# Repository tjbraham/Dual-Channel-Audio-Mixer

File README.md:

# Dual-Channel 3-Band Analog Audio Mixer PCB

A custom single-supply ($9\text{ V}$) dual-channel analog audio mixer featuring a 3-band Linkwitz-Riley ($Q = 0.5$) Sallen-Key active crossover network, $180^\circ$ mid-band phase inversion for flat summation, and an inverting summing architecture designed in **LTspice** and **KiCad** for automated SMT assembly.

---

## Hardware Overview & Key Specifications

| Parameter | Specification |
| :--- | :--- |
| **Channels** | 2 Independent Stereo-to-Mono Input Channels (`J7`, `J8`) + 1 Master Output (`J9`) |
| **Filter Topology** | 2nd-Order Unity-Gain Sallen-Key Active Crossover ($Q = 0.5$, $-6\text{ dB}$ at $f_c$) |
| **Frequency Bands** | **Low:** $< 102.6\text{ Hz}$ \| **Mid:** $102.6\text{ Hz} - 4.98\text{ kHz}$ \| **High:** $> 4.98\text{ kHz}$ |
| **Active ICs** | $4\times$ `TL074CDT` Quad JFET-Input Operational Amplifiers (`SOIC-14`) |
| **Power Supply** | $9\text{ V}$ Single-Supply (`BT1` / `SW1`) with $4.5\text{ V}$ Virtual Ground (`VRef`) |
| **PCB Dimensions** | $87.11\text{ mm} \times 51.33\text{ mm}$ ($3.43\text{ in} \times 2.02\text{ in}$), 2-Layer `FR-4` ($1.6\text{ mm}$, $1\text{ oz}$ Cu) |
| **Component Count** | 89 Total Designators (69 `0805`/`SOIC-14` SMD Parts + 20 Through-Hole/DFT Items) |

---

## Circuit Architecture & Engineering Decisions

### 1. Input Stage & Single-Supply Virtual Reference (`VRef`)
* **Passive Stereo-to-Mono Input Summing:** Each $3.5\text{ mm}$ TRS input jack (`J7` and `J8`) sums Left (Tip) and Right (Ring) channels through matched $1\text{ k}\Omega$ resistors (`R10`/`R11` and `R20`/`R21`), providing a $500\ \Omega$ effective source impedance before AC coupling through $10\ \mu\text{F}$ capacitors (`C2`, `C3`) and biasing to `VRef` via $1\text{ M}\Omega$ resistors (`R9`, `R22`).
* **Virtual Ground Generation (`VRef = 4.5V`):** Because the circuit operates from a single $9\text{ V}$ battery (`BT1`), a $10\text{ k}\Omega / 10\text{ k}\Omega$ voltage divider (`R3`, `R4`) bypassed with a $10\ \mu\text{F}$ capacitor (`C1`, $f_c = 3.18\text{ Hz}$) establishes a low-noise $4.5\text{ V}$ mid-rail reference (`VRef`) for all op-amp non-inverting inputs and filter bias paths.
* **Click-Free Potentiometer Biasing:** All six $10\text{ k}\Omega$ band-level potentiometers (`RV1`–`RV6`) tie their reference terminals directly to `VRef` rather than `GND`. Keeping the wiper and the op-amp summing nodes at an identical $4.5\text{ V}$ DC potential eliminates DC current flow through the potentiometer wipers, preventing scratchy audio noise when adjusting EQ levels.

### 2. 3-Band Sallen-Key Crossover & Impedance Scaling
Each input channel splits into three parallel active filter branches designed around equal-$`R`$, equal-$`C`$ unity-gain Sallen-Key topologies ($Q = 0.5$):
* **Low-Pass Band (`U1A`, `U2C`):** Uses $R = 3.3\text{ k}\Omega$ (`R26`/`R27`, `R12`/`R13`) and $C = 470\text{ nF}$ (`C9`/`C10`, `C21`/`C22`) to set a cutoff frequency of:
  $$f_{c,\text{LP}} = \frac{1}{2\pi (3.3\text{ k}\Omega)(470\text{ nF})} = 102.61\text{ Hz}$$
* **High-Pass Band (`U1B`, `U2D`) & Impedance Scaling:** Uses $C = 4.7\text{ nF}$ (`C13`/`C14`, `C5`/`C7`) and $R = 6.8\text{ k}\Omega$ (`R30`/`R31`, `R14`/`R42`) to set a cutoff frequency of:
  $$f_{c,\text{HP}} = \frac{1}{2\pi (6.8\text{ k}\Omega)(4.7\text{ nF})} = 4979.82\text{ Hz}$$
  Scaling the high-frequency filter impedances up by $100\times$ (from $68\ \Omega / 470\text{ nF}$ to $6.8\text{ k}\Omega / 4.7\text{ nF}$) prevents the high-pass stage from loading down the unbuffered $500\ \Omega$ input node and avoids overloading the `TL074` output stages.
* **Mid Band-Pass Cascade & $180^\circ$ Phase Inversion (`U1C` $\rightarrow$ `U1D` $\rightarrow$ `U2A` & `U3A` $\rightarrow$ `U3B` $\rightarrow$ `U3C`):** Cascades a $102.61\text{ Hz}$ Sallen-Key high-pass filter ($3.3\text{ k}\Omega$, $470\text{ nF}$) into a $4979.82\text{ Hz}$ Sallen-Key low-pass filter ($6.8\text{ k}\Omega$, $4.7\text{ nF}$). Because 2nd-order low-pass and high-pass filters introduce $\pm 90^\circ$ phase shifts at their crossover frequencies, summing them in-phase would create deep $-30\text{ dB}$ cancellation notches at $100\text{ Hz}$ and $5\text{ kHz}$; routing the Mid band through a dedicated unity-gain inverting amplifier (`U2A` with `R1`/`R2` $= 10\text{ k}\Omega$; `U3C` with `R34`/`R46` $= 10\text{ k}\Omega$) flips the Mid band by $180^\circ$ to achieve a flat $0.00\text{ dB}$ acoustic sum across $20\text{ Hz} - 20\text{ kHz}$.

### 3. Channel & Master Summing Stages
* **Channel Summing Amplifiers (`U2B`, `U3D`):** Sum the three EQ potentiometer wipers (`RV1`–`RV3` for Channel 1; `RV4`–`RV6` for Channel 2) through $100\text{ k}\Omega$ input resistors (`R5`–`R7`, `R16`–`R18`) with $100\text{ k}\Omega$ feedback resistors (`R8`, `R19`).
* **Master Summer & Output Coupling (`U4A`):** Sums both channels (`R23`, `R24` $= 100\text{ k}\Omega$) with unity feedback (`R25` $= 100\text{ k}\Omega$), AC-couples the final output through a $10\ \mu\text{F}$ blocking capacitor (`C4`) with a $100\text{ k}\Omega$ ground bleed resistor (`R35`, $f_c = 1.75\text{ Hz}$ into a $10\text{ k}\Omega$ line load), and drives both Tip and Ring of the output jack (`J9`).

---

## PCB Layout, DFM, & Design for Test (DFT)

* **Split Reference Planes:** The 2-layer PCB routes primary signal traces alongside a top-layer `VRef` copper pour (`F.Cu`) and a continuous bottom-layer `GND` return plane (`B.Cu`), providing low-impedance reference paths and shielding sensitive summing nodes from crosstalk.
* **Power Integrity & Op-Amp Termination:** Four local $100\text{ nF}$ (`0805`, X7R) decoupling capacitors (`C17`–`C20`) are placed within $5.8\text{ mm} - 6.9\text{ mm}$ of the `V+` pin (Pin 4) of each `TL074` (`U1`–`U4`) with direct vias to the bottom `GND` plane. Unused op-amp channels on `U4` (`U4B`, `U4C`, `U4D`) are configured as unity-gain followers tied to `VRef` to prevent floating-input oscillation and excess quiescent current draw.
* **Onboard DFT Test Points:** Eight $1.5\text{ mm} \times 1.5\text{ mm}$ bare-copper surface-mount test pads allow safe oscilloscope and multimeter probing during bring-up:
  * **DC Power Rails:** `9V_test1`, `Vref_test1`, `gnd_test1`
  * **AC Signal Chain:** `top_in_test1`, `bot_in_test1`, `top_out_test1`, `bot_out_test1`, `fin_out_test1`
* **Mechanical Integration:** Includes four $3.2\text{ mm}$ `M3` corner mounting holes for enclosure standoffs and custom `Edge.Cuts` slots to recess the barrels of the three horizontal $3.5\text{ mm}$ TRS audio jacks (`J7`–`J9`) flush with the board perimeter.

---

## Bill of Materials (JLCPCB SMT & Hand-Soldered Parts)

### Automated SMT Assembly Components
| Designators | Qty | Value | Package | LCSC Part # | Description / MPN |
| :--- | :---: | :---: | :---: | :---: | :--- |
| `C1, C2, C3, C4` | 4 | $10\ \mu\text{F}$ | `0805` | `C15850` | 25V X5R $\pm 10\%$ MLCC (`CL21A106KAYNNNE`) |
| `C6, C8, C9, C10, C11, C12, C21, C22` | 8 | $470\text{ nF}$ | `0805` | `C13967` | 50V X7R $\pm 10\%$ MLCC (`CL21B474KBFNNNE`) |
| `C5, C7, C13, C14, C15, C16, C23, C24` | 8 | $4.7\text{ nF}$ | `0805` | `C1744` | 50V X7R $\pm 10\%$ MLCC (`0805B472K500NT`) |
| `C17, C18, C19, C20` | 4 | $100\text{ nF}$ | `0805` | `C49678` | 50V X7R $\pm 10\%$ MLCC (`CC0805KRX7R9BB104`) |
| `R10, R11, R20, R21` | 4 | $1\text{ k}\Omega$ | `0805` | `C17513` | $\pm 1\%$ 1/8W Thick Film (`0805W8F1001T5E`) |
| `R12, R13, R15, R26-R29, R36, R43` | 9 | $3.3\text{ k}\Omega$ | `0805` | `C26010` | $\pm 1\%$ 1/8W Thick Film (`0805W8F3301T5E`) |
| `R14, R30-R33, R42, R44, R45` | 8 | $6.8\text{ k}\Omega$ | `0805` | `C17772` | $\pm 1\%$ 1/8W Thick Film (`0805W8F6801T5E`) |
| `R1-R4, R34, R46` | 6 | $10\text{ k}\Omega$ | `0805` | `C17414` | $\pm 1\%$ 1/8W Thick Film (`0805W8F1002T5E`) |
| `R5-R8, R16-R19, R23-R25, R35` | 12 | $100\text{ k}\Omega$ | `0805` | `C149504` | $\pm 1\%$ 1/8W Thick Film (`0805W8F1003T5E`) |
| `R9, R22` | 2 | $1\text{ M}\Omega$ | `0805` | `C17514` | $\pm 1\%$ 1/8W Thick Film (`0805W8F1004T5E`) |
| `U1, U2, U3, U4` | 4 | `TL074` | `SOIC-14` | `C6963` | Quad JFET Op-Amp (`TL074CDT`) |

### Hand-Soldered Through-Hole Components
| Designators | Qty | Footprint | Description |
| :--- | :---: | :--- | :--- |
| `J7, J8, J9` | 3 | `Jack_3.5mm_CUI_SJ1-3525N_Horizontal` | $3.5\text{ mm}$ Stereo TRS Audio Jack (`CUI SJ1-3525N`) |
| `RV1-RV6` | 6 | `PinHeader_1x03_P2.54mm_Vertical` | $1\times 3$ Header ($2.54\text{ mm}$) for $10\text{ k}\Omega$ Linear Potentiometers (`Low`, `Mid`, `High`) |
| `BT1, SW1` | 2 | `PinHeader_1x02_P2.54mm_Vertical` | $1\times 2$ Header ($2.54\text{ mm}$) for $9\text{ V}$ Battery Snap & SPST Power Switch |
| `D1` | 1 | `LED_D5.0mm` | $5\text{ mm}$ Through-Hole Power Indicator LED |

---

## Hardware Bring-Up & Testing Procedure

1. **Visual & Continuity Inspection:** Inspect all `SOIC-14` pins and `0805` pads after SMT delivery; verify with a digital multimeter (DMM) in continuity mode that no short exists between `9V_test1`, `Vref_test1`, and `gnd_test1` before soldering through-hole connectors.
2. **DC Power Rail Verification:** Connect a $9\text{ V}$ source to `BT1`, close `SW1`, confirm `D1` illuminates ($\sim 2.1\text{ mA}$ bias via `R36`), and probe `9V_test1` ($+9.0\text{ V}$) and `Vref_test1` ($+4.50\text{ V} \pm 0.05\text{ V}$) relative to `gnd_test1`.
3. **AC Signal Injection & Crossover Sweep:** Inject a $1\text{ V}_{\text{pp}}$ sine wave from a function generator into `J7` (`top_in_test1`) and `J8` (`bot_in_test1`) across $20\text{ Hz} - 20\text{ kHz}$ ($100\text{ Hz}$, $1\text{ kHz}$, and $10\text{ kHz}$ test points) while monitoring `top_out_test1`, `bot_out_test1`, and `fin_out_test1` on an oscilloscope to verify band isolation, $-6\text{ dB}$ crossover points, and clean summation.

---

## Repository Structure

```text
├── Docs/
│   ├── Audio_Mixer_PCB_schematic.pdf       # Full KiCad 10.0 schematic diagram
│   ├── pcb_3d_render.png                   # 3D board render
│   └── Audio_Mixer_PCB.pdf                 # F.Cu (VRef) and B.Cu (GND) copper views
│   └── Audio_Mixer_LTspice.pdf             # LTSpice diagram PDF
├── Schematic_and_PCB/
│   ├── production/                         # KiCad JLCPCB formatted production files
│       ├── bom.csv                         # JLCPCB-formatted Bill of Materials with LCSC numbers
│       └── positions.csv                   # Component Placement List (CPL) for SMT pick-and-place
│       └── Audio_Mixer_PCB_schematic.zip   # PCB Gerber and Drill files
├── Simulation/
│   └── Two_Channel_Audio_Mixer.asc         # LTspice active filter & summing simulation
├── Audio_Mixer_PCB.kicad_pro               # KiCad project file
├── Audio_Mixer_PCB.kicad_sch               # KiCad schematic file
├── Audio_Mixer_PCB.kicad_pcb               # KiCad 2-layer PCB layout file
└── README.md
```

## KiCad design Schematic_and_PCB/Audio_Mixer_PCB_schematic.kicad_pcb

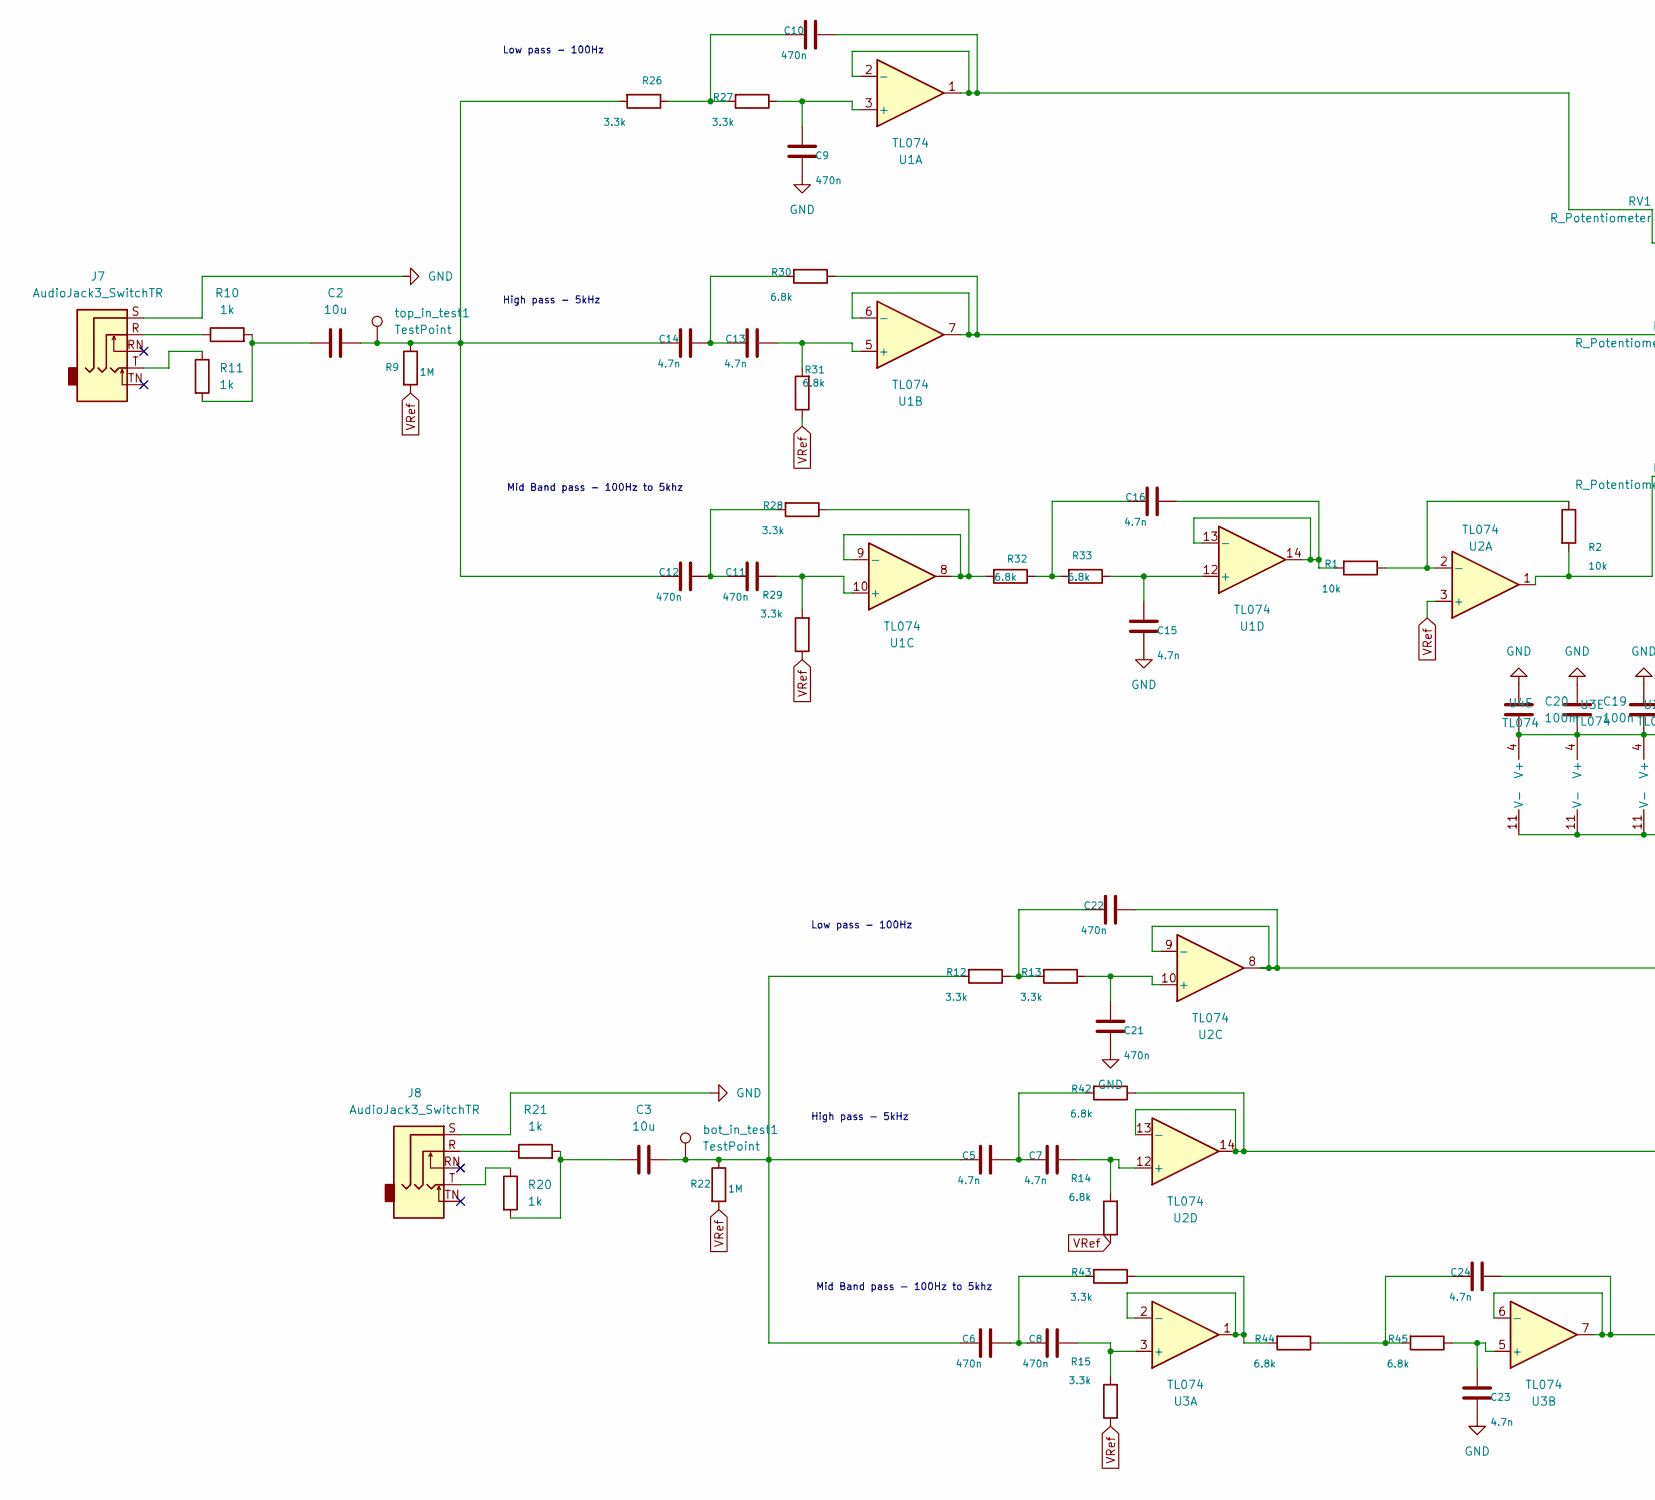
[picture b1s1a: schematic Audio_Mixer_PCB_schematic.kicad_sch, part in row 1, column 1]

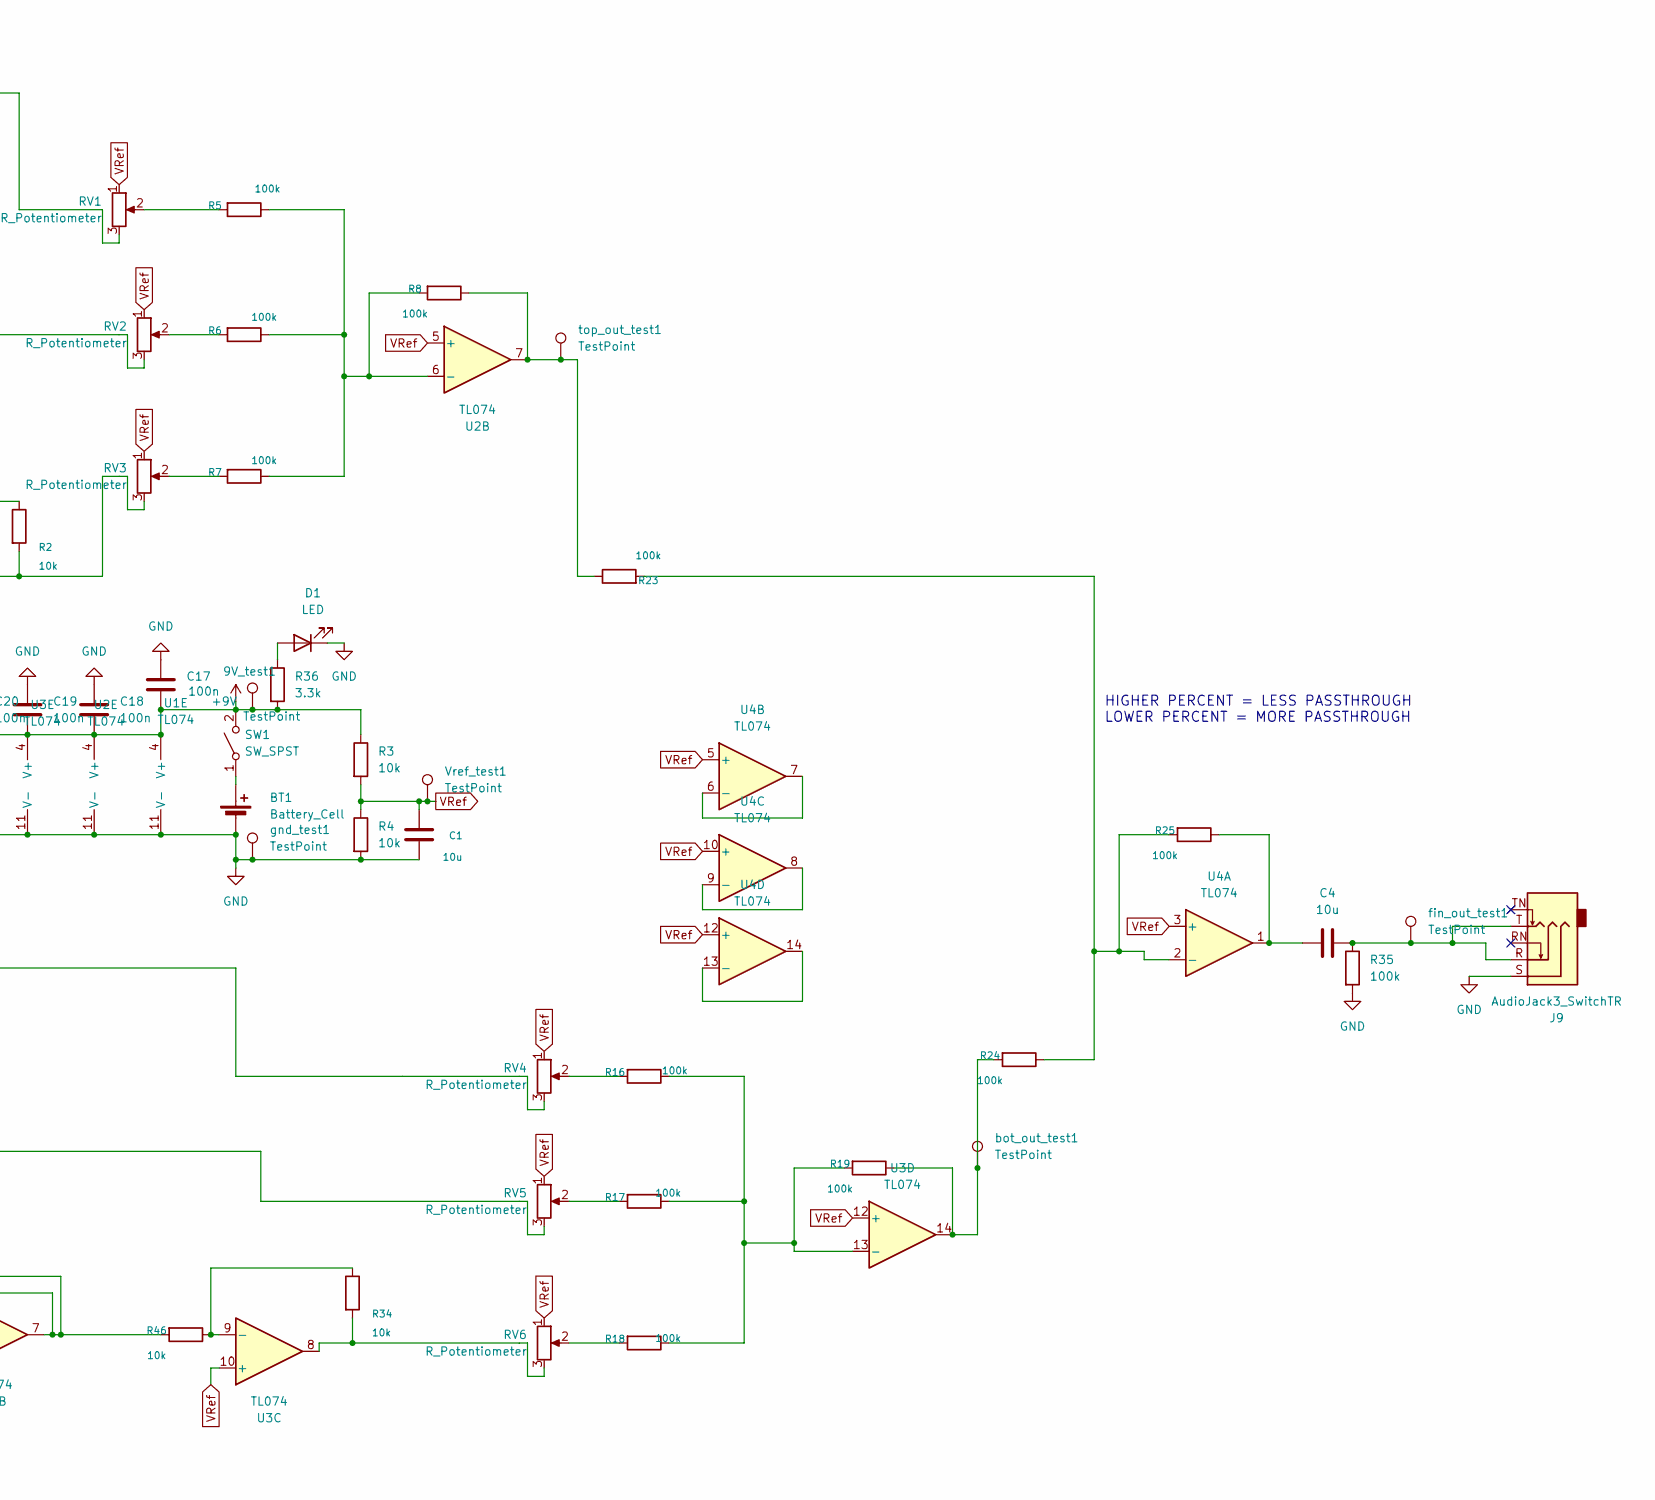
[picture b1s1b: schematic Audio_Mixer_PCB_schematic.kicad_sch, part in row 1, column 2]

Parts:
9V_test1: TestPoint; TestPoint_Pad_1.5x1.5mm
BT1: Battery_Cell; PinHeader_1x02_P2.54mm_Vertical
C1, C2, C3, C4: 10u; C_0805_2012Metric_Pad1.18x1.45mm_HandSolder; LCSC C15850
C5, C7, C13, C14, C15, C16, C23, C24: 4.7n; C_0805_2012Metric_Pad1.18x1.45mm_HandSolder; LCSC C1744
C6, C8, C9, C10, C11, C12, C21, C22: 470n; C_0805_2012Metric_Pad1.18x1.45mm_HandSolder; LCSC C13967
C17, C18, C19, C20: 100n; C_0805_2012Metric_Pad1.18x1.45mm_HandSolder; LCSC C49678
D1: LED; LED_D5.0mm
J7, J8, J9: AudioJack3_SwitchTR; Jack_3.5mm_CUI_SJ1-3525N_Horizontal
R1, R2, R3, R4, R34, R46: 10k; R_0805_2012Metric_Pad1.20x1.40mm_HandSolder; LCSC C17414
R5, R6, R7, R8, R16, R17, R18, R19, R23, R24, R25, R35: 100k; R_0805_2012Metric_Pad1.20x1.40mm_HandSolder; LCSC C149504
R9, R22: 1M; R_0805_2012Metric_Pad1.20x1.40mm_HandSolder; LCSC C17514
R10, R11, R20, R21: 1k; R_0805_2012Metric_Pad1.20x1.40mm_HandSolder; LCSC C17513
R12, R13, R15, R26, R27, R28, R29, R36, R43: 3.3k; R_0805_2012Metric_Pad1.20x1.40mm_HandSolder; LCSC C26010
R14, R30, R31, R32, R33, R42, R44, R45: 6.8k; R_0805_2012Metric_Pad1.20x1.40mm_HandSolder; LCSC C17772
RV1, RV2, RV3, RV4, RV5, RV6: R_Potentiometer; PinHeader_1x03_P2.54mm_Vertical
SW1: SW_SPST; PinHeader_1x02_P2.54mm_Vertical
U1, U2, U3, U4: TL074; SOIC-14_3.9x8.7mm_P1.27mm; LCSC C6963
Vref_test1: TestPoint; TestPoint_Pad_1.5x1.5mm
bot_in_test1: TestPoint; TestPoint_Pad_1.5x1.5mm
bot_out_test1: TestPoint; TestPoint_Pad_1.5x1.5mm
fin_out_test1: TestPoint; TestPoint_Pad_1.5x1.5mm
gnd_test1: TestPoint; TestPoint_Pad_1.5x1.5mm
top_in_test1: TestPoint; TestPoint_Pad_1.5x1.5mm
top_out_test1: TestPoint; TestPoint_Pad_1.5x1.5mm

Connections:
+9V: 9V_test1.1 (1_1), C17.1, C18.2, C19.2, C20.2, R3.1, R36.2, SW1.2 (B), U1.4 (V+), U2.4 (V+), U3.4 (V+), U4.4 (V+)
GND: BT1.2 (-), C1.2, C9.2, C15.2, C17.2, C18.1, C19.1, C20.1, C21.2, C23.2, D1.1 (K), J7.S, J8.S, J9.S, R4.2, R35.2, U1.11 (V-), U2.11 (V-), U3.11 (V-), U4.11 (V-), gnd_test1.1 (1_1)
unnamed: BT1.1 (+), SW1.1 (A)
unnamed: C2.1, R10.2, R11.2
unnamed: C3.1, R20.2, R21.2
unnamed: C3.2, C5.2, C6.2, R12.2, R22.1, bot_in_test1.1 (1_1)
unnamed: C4.1, R25.1, U4.1
unnamed: C4.2, J9.R, J9.T, R35.1, fin_out_test1.1 (1_1)
unnamed: C5.1, C7.2, R42.2
unnamed: C6.1, C8.2, R43.2
unnamed: C10.2, R26.1, R27.2
unnamed: C11.2, C12.1, R28.2
unnamed: C2.2, C12.2, C14.2, R9.1, R26.2, top_in_test1.1 (1_1)
unnamed: C13.2, C14.1, R30.2
unnamed: C16.2, R32.1, R33.2
unnamed: C22.2, R12.1, R13.2
unnamed: C24.2, R44.1, R45.2
unnamed: D1.2 (A), R36.1
unnamed: J7.R, R10.1
unnamed: J7.T, R11.1
unnamed: J8.R, R21.1
unnamed: J8.T, R20.1
unnamed: R2.2, RV3.3, U2.1
unnamed: R5.2, RV1.2
unnamed: R6.2, RV2.2
unnamed: R7.2, RV3.2
unnamed: R16.2, RV4.2
unnamed: R17.2, RV5.2
unnamed: R18.2, RV6.2
unnamed: R19.1, R24.2, U3.14, bot_out_test1.1 (1_1)
unnamed: R8.1, R23.1, U2.7, top_out_test1.1 (1_1)
unnamed: R34.2, RV6.3, U3.8
unnamed: C9.1, R27.1, U1.3 (+)
unnamed: C10.1, RV1.3, U1.1, U1.2 (-)
unnamed: C13.1, R31.2, U1.5 (+)
unnamed: R30.1, RV2.3, U1.6 (-), U1.7
unnamed: C11.1, R29.2, U1.10 (+)
unnamed: R28.1, R32.2, U1.8, U1.9 (-)
unnamed: C15.1, R33.1, U1.12 (+)
unnamed: C16.1, R1.2, U1.13 (-), U1.14
unnamed: R1.1, R2.1, U2.2 (-)
unnamed: R5.1, R6.1, R7.1, R8.2, U2.6 (-)
unnamed: C21.1, R13.1, U2.10 (+)
unnamed: C22.1, RV4.3, U2.8, U2.9 (-)
unnamed: C7.1, R14.2, U2.12 (+)
unnamed: R42.1, RV5.3, U2.13 (-), U2.14
unnamed: C8.1, R15.2, U3.3 (+)
unnamed: R43.1, R44.2, U3.1, U3.2 (-)
unnamed: C23.1, R45.1, U3.5 (+)
unnamed: C24.1, R46.2, U3.6 (-), U3.7
unnamed: R34.1, R46.1, U3.9 (-)
unnamed: R16.1, R17.1, R18.1, R19.2, U3.13 (-)
unnamed: R23.2, R24.1, R25.2, U4.2 (-)
unnamed: U4.6 (-), U4.7
unnamed: U4.8, U4.9 (-)
unnamed: U4.13 (-), U4.14
VRef: C1.1, R3.2, R4.1, R9.2, R14.1, R15.1, R22.2, R29.1, R31.1, RV1.1, RV2.1, RV3.1, RV4.1, RV5.1, RV6.1, U2.3 (+), U2.5 (+), U3.10 (+), U3.12 (+), U4.3 (+), U4.5 (+), U4.10 (+), U4.12 (+), Vref_test1.1 (1_1)

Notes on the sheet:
High pass - 5kHz
Low pass - 100Hz
Mid Band pass - 100Hz to 5khz
HIGHER PERCENT = LESS PASSTHROUGH LOWER PERCENT = MORE PASSTHROUGH

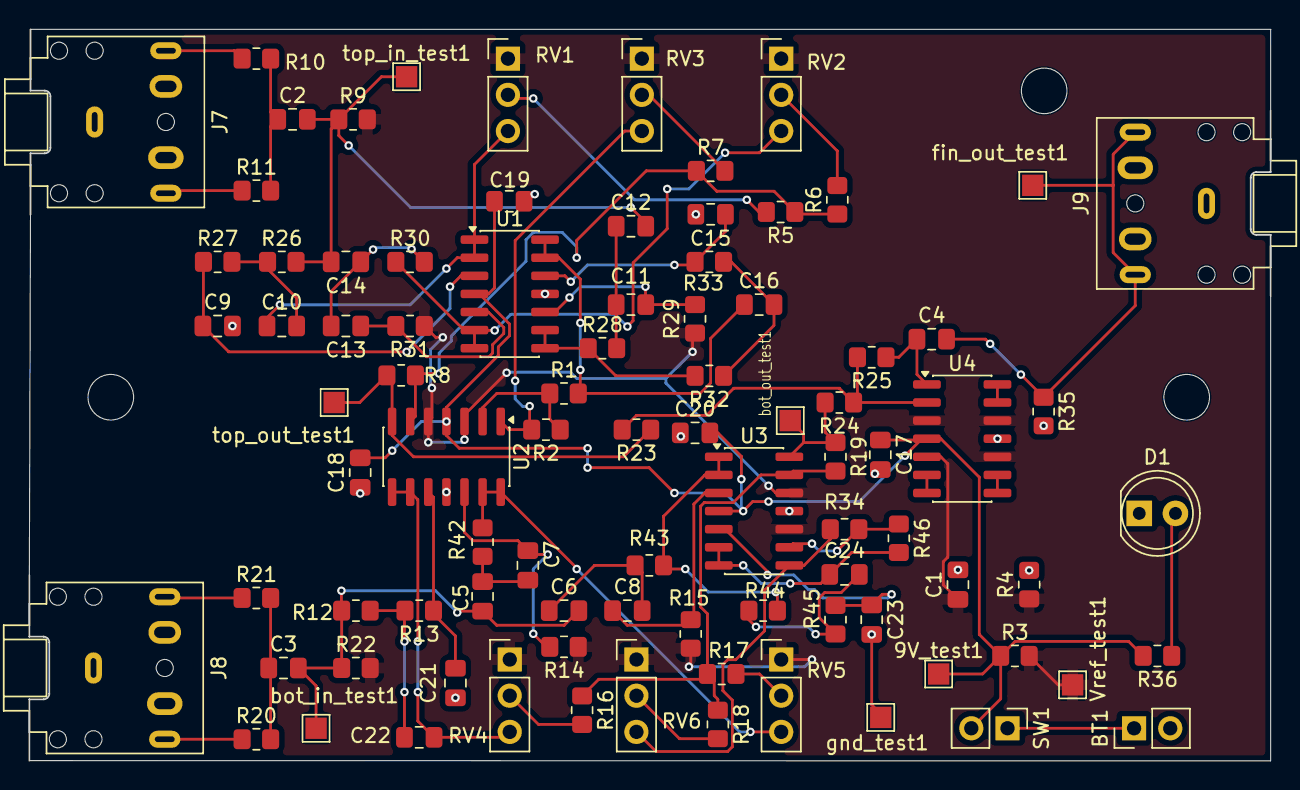
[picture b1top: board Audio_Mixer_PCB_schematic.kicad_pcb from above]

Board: 2 copper layers, 87.1 x 51.3 mm, 89 parts (0 on the bottom side), 57 nets.

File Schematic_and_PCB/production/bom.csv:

Designator,Footprint,Quantity,Value,LCSC Part #
"9V_TEST1, BOT_IN_TEST1, BOT_OUT_TEST1, FIN_OUT_TEST1, GND_TEST1, TOP_IN_TEST1, TOP_OUT_TEST1, VREF_TEST1",TestPoint_Pad_1.5x1.5mm,8,TestPoint,
BT1,PinHeader_1x02_P2.54mm_Vertical,1,Battery_Cell,
"C1, C2, C3, C4",0805,4,10u,C15850
"C10, C11, C12, C21, C22, C6, C8, C9",0805,8,470n,C13967
"C13, C14, C15, C16, C23, C24, C5, C7",0805,8,4.7n,C1744
"C17, C18, C19, C20",0805,4,100n,C49678
D1,LED_D5.0mm,1,LED,
"J7, J8, J9",Jack_3.5mm_CUI_SJ1-3525N_Horizontal,3,AudioJack3_SwitchTR,
"R1, R2, R3, R34, R4, R46",0805,6,10k,C17414
"R10, R11, R20, R21",0805,4,1k,C17513
"R12, R13, R15, R26, R27, R28, R29, R36, R43",0805,9,3.3k,C26010
"R14, R30, R31, R32, R33, R42, R44, R45",0805,8,6.8k,C17772
"R16, R17, R18, R19, R23, R24, R25, R35, R5, R6, R7, R8",0805,12,100k,C149504
"R22, R9",0805,2,1M,C17514
"RV1, RV2, RV3, RV4, RV5, RV6",PinHeader_1x03_P2.54mm_Vertical,6,R_Potentiometer,
SW1,PinHeader_1x02_P2.54mm_Vertical,1,SW_SPST,
"U1, U2, U3, U4",SOIC-14_3.9x8.7mm_P1.27mm,4,TL074,C6963
